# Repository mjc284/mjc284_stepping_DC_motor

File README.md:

# mjc284_stepping_DC_motor
Complete software and hardware build of a stepping DC motor using permanent magnets.

### Video demonstration:
https://www.youtube.com/watch?v=WFz_ZSToyOA

### Concept:

The main focus of this project was to find a way to precisely control the angle of a DC motor in a similar way to stepper motors. This was achieved by attaching permenant magnets to the DC motor shaft, and creating magnetic potential 'wells' around the shaft for the rotor to fall into. In simple terms, the rotor magnet wants to be adjacent to opposite poles on the stator, giving the rotor only 3 possible states to rest on. Therefore, the motor would be driven by pulses to 'step' from one state from another, which is similar to how a stepper motor moves (although the driving operation is different). 

The output of the rotor was geared down to drive a numbered disc which represents a clock. On the electrical side, a 3-legged inverter that I designed for general purpose was used, where only two of the legs were utilized as an H-bridge. The motor 'stepping' was driven in a sequence as follows: a clockwise pulse, momentary off-state, a shorter anticlockwise pulse, and finally an off state. The anticlockwise pulse was necessary to prevent the rotor from rotating beyond the next desired state.

### Project Workflow:
- All the hardware and circuit were modelled using Fusion 360.
- Some of the parts were machined from 6mm MDF using a desktop-CNC. 
- Some of the parts were 3D-printed with postprocessing from Ultimaker-Cura.
- PCB was manufactured from the Fusion 360 gerber file by Chinese PCB services.
- Arduino-pro mini was programmed and used to drive the circuit.

### Possible Improvements:
- A better way to machine the parts with better accuracy would prevent the rotor from skipping steps occasionally.
- The rotor oscillates when it falls into the magnetic potential well. Perhaps this may be modelled as a harmonic oscillator and the stator dampened critically to prevent such oscillations.

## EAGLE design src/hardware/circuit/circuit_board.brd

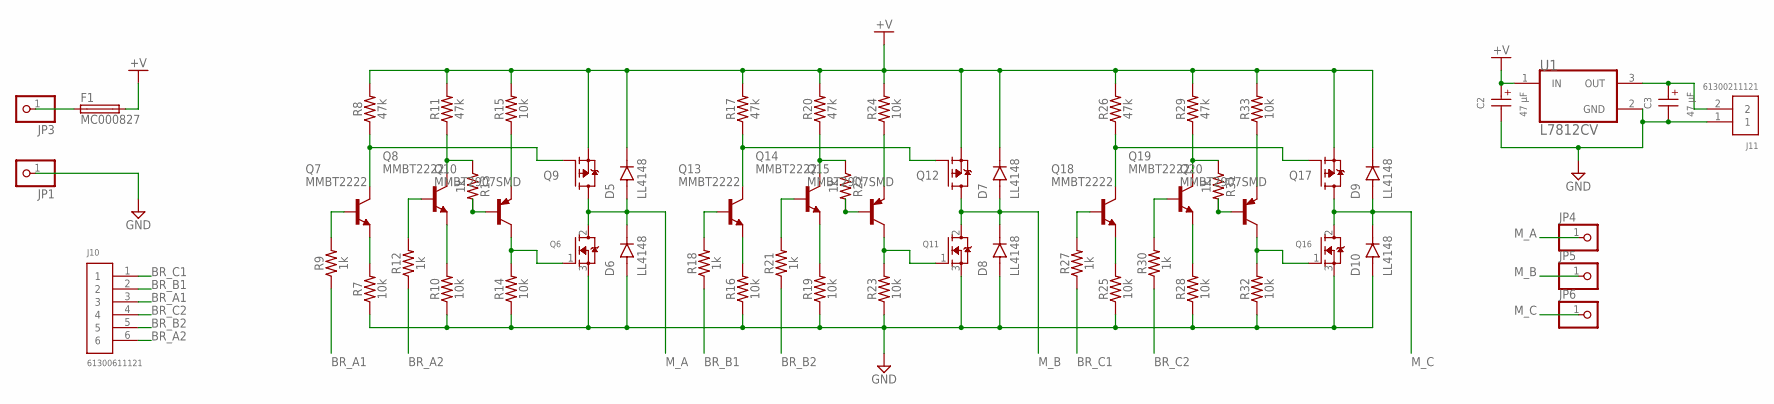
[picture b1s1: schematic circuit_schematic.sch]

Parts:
C2, C3: 47 µF; WCAP-ATET_5X11(DXL)
D5, D6, D7, D8, D9, D10: LL4148; DIO_LL4148
F1: MC000827
J10: 61300611121
J11: 61300211121
JP1, JP3, JP4, JP5, JP6: PINHD-1X1; 1X01
Q6, Q11, Q16: MOSFET-NGDS_TO220V; TO220V
Q7, Q8, Q13, Q14, Q18, Q19: MMBT2222; SOT23-BEC
Q9, Q12, Q17: MOSFET-PGDS_TO220V; TO220V
Q10, Q15, Q20: MMBT2907SMD; SOT23-BEC
R7, R10, R14, R15, R16, R19, R23, R24, R25, R28, R32, R33: 10k; 1206
R8, R11, R17, R20, R26, R29: 47k; 1206
R9, R12, R13, R18, R21, R22, R27, R30, R31: 1k; 1206
U1: L7812CV; TO-220-3

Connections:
+V: C2.1 (+), D5.C, D7.C, D9.C, F1.P$2 (2), Q9.3 (S), Q12.3 (S), Q17.3 (S), R8.2, R11.2, R15.2, R17.2, R20.2, R24.2, R26.2, R29.2, R33.2, U1.1 (IN)
BR_A1: J10.3, R9.1
BR_A2: J10.6, R12.1
BR_B1: J10.2, R18.1
BR_B2: J10.5, R21.1
BR_C1: J10.1, R27.1
BR_C2: J10.4, R30.1
GND: C2.2 (-), C3.2 (-), D6.A, D8.A, D10.A, J11.1, JP1.1, Q6.3 (S), Q11.3 (S), Q16.3 (S), R7.1, R10.1, R14.1, R16.1, R19.1, R23.1, R25.1, R28.1, R32.1, U1.2 (GND)
M_A: D5.A, D6.C, JP4.1, Q6.2 (D), Q9.2 (D)
M_B: D7.A, D8.C, JP5.1, Q11.2 (D), Q12.2 (D)
M_C: D9.A, D10.C, JP6.1, Q16.2 (D), Q17.2 (D)
unnamed: Q8.C, R11.1, R13.1
unnamed: Q8.B, R12.2
unnamed: Q8.E, R10.2
unnamed: Q6.1 (G), Q10.C, R14.2
unnamed: Q10.E, R15.1
unnamed: Q7.B, R9.2
unnamed: Q7.C, Q9.1 (G), R8.1
unnamed: Q7.E, R7.2
unnamed: Q10.B, R13.2
unnamed: F1.P$1 (1), JP3.1
unnamed: Q14.C, R20.1, R22.1
unnamed: Q14.B, R21.2
unnamed: Q14.E, R19.2
unnamed: Q11.1 (G), Q15.C, R23.2
unnamed: Q15.E, R24.1
unnamed: Q13.B, R18.2
unnamed: Q12.1 (G), Q13.C, R17.1
unnamed: Q13.E, R16.2
unnamed: C3.1 (+), J11.2, U1.3 (OUT)
unnamed: Q15.B, R22.2
unnamed: Q19.C, R29.1, R31.1
unnamed: Q19.B, R30.2
unnamed: Q19.E, R28.2
unnamed: Q16.1 (G), Q20.C, R32.2
unnamed: Q20.E, R33.1
unnamed: Q18.B, R27.2
unnamed: Q17.1 (G), Q18.C, R26.1
unnamed: Q18.E, R25.2
unnamed: Q20.B, R31.2

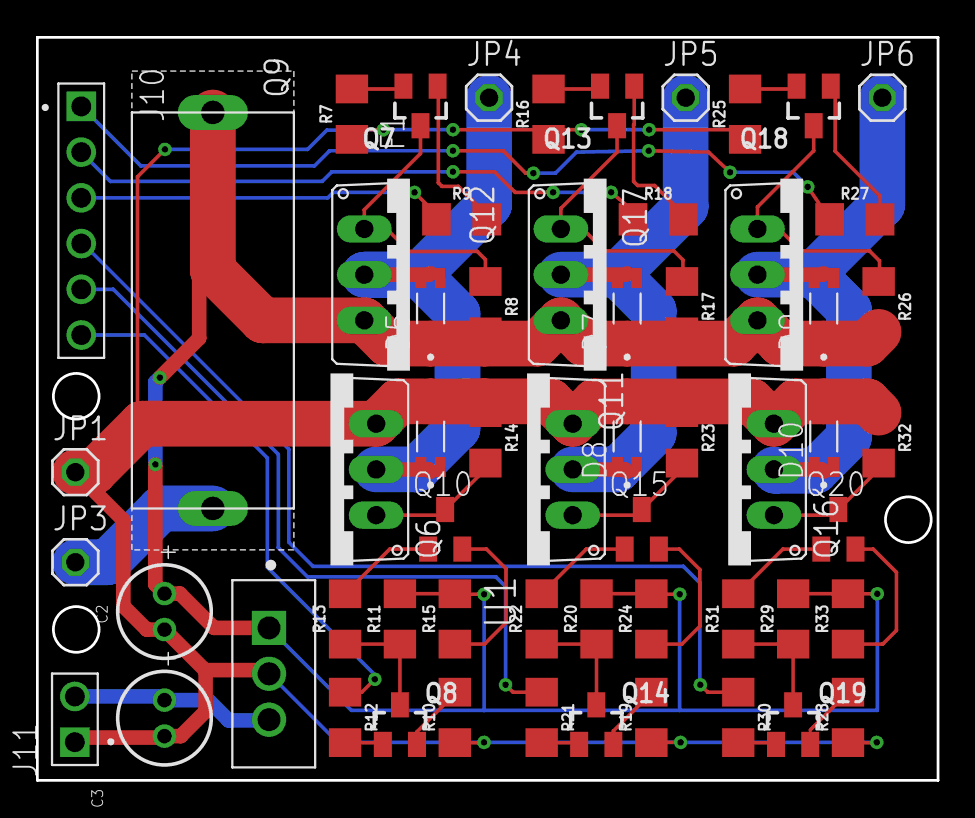
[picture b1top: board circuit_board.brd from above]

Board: 2 copper layers, 50.0 x 41.3 mm, 59 parts (0 on the bottom side), 40 nets.

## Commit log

2022-10-02 Initiated repository.
2022-10-02 Changed src name

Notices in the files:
parts and their libraries:
SparkFun-Resistors: Licensing: Creative Commons ShareAlike 4.0 International - https://creativecommons.org/licenses/by-sa/4.0
Wurth_Capacitors_WCAP-ATET: Copyright: Würth Elektronik
